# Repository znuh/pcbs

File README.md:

# pcbs
various printed circuit boards

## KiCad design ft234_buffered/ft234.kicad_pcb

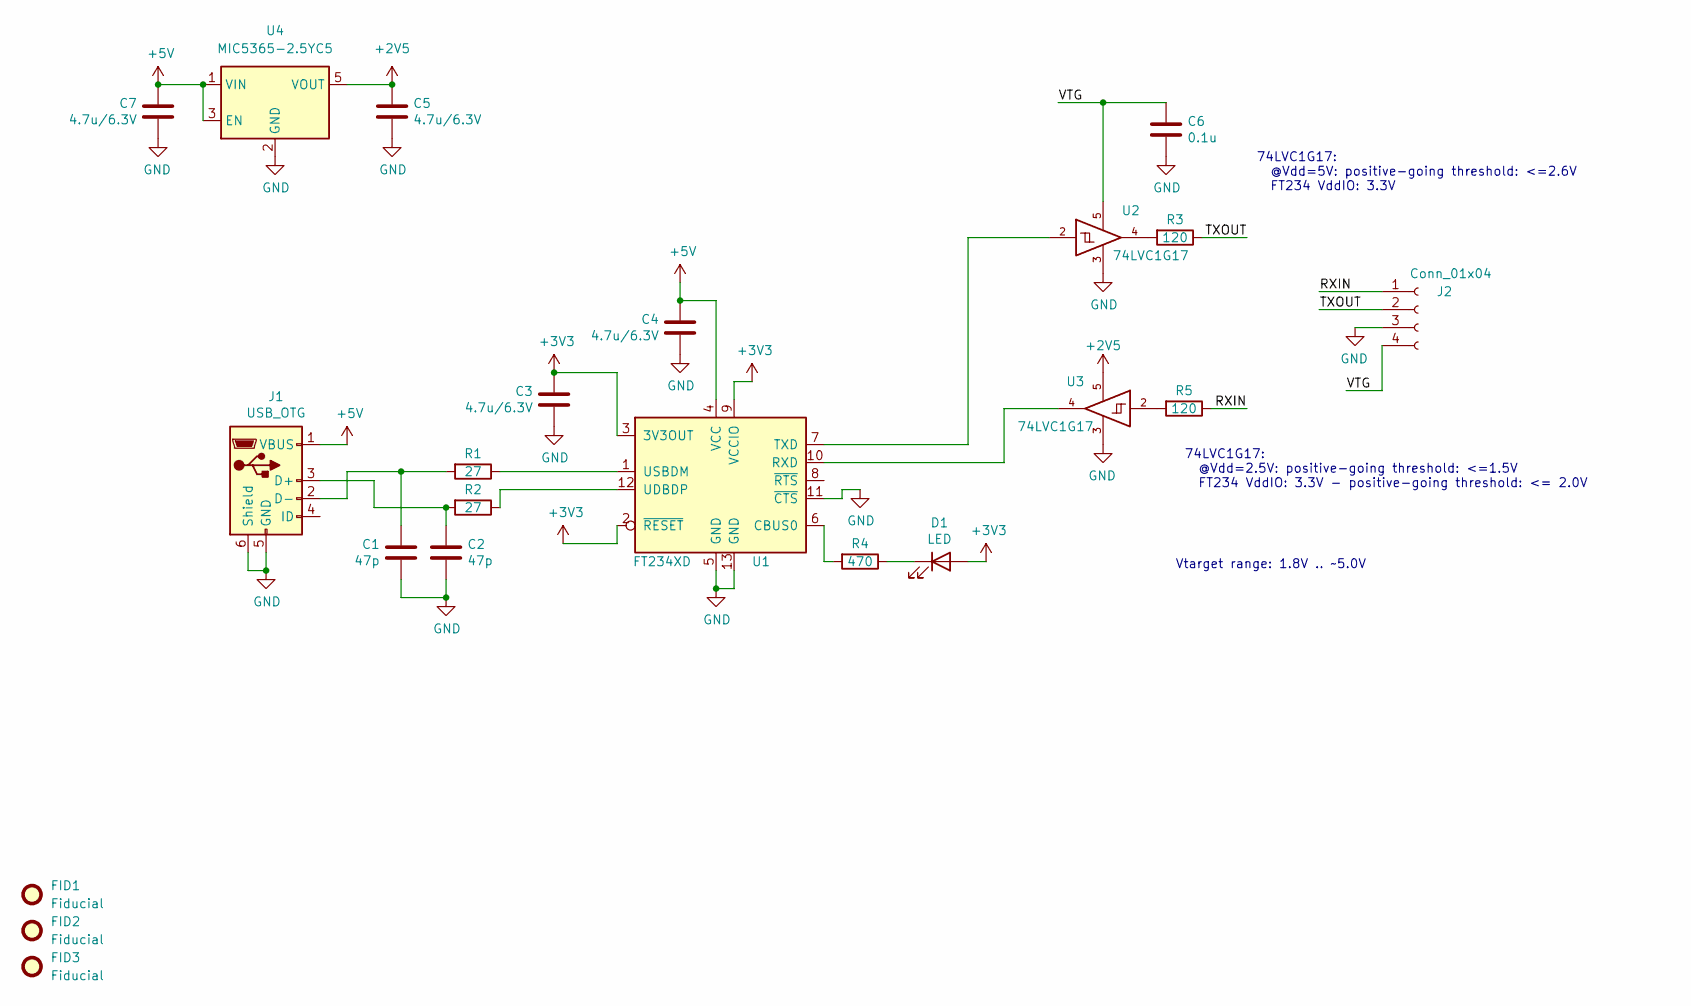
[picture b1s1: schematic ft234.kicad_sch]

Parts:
C1, C2: 47p; C_0402_1005Metric
C3, C4, C5, C7: 4.7u/6.3V; C_0402_1005Metric
C6: 0.1u; C_0402_1005Metric
D1: LED; LED_0603_1608Metric
FID1, FID2, FID3: Fiducial; Fiducial_0.5mm_Mask1mm
J1: USB_OTG; USB_Micro-B_Amphenol_10103594-0001LF_Horizontal
J2: Conn_01x04; PinHeader_1x04_P2.54mm_Vertical
R1, R2: 27; R_0402_1005Metric
R3, R5: 120; R_0402_1005Metric
R4: 470; R_0402_1005Metric
U1: FT234XD; DFN-12-1EP_3x3mm_P0.45mm_EP1.66x2.38mm
U2, U3: 74LVC1G17; TSOP-5_1.65x3.05mm_P0.95mm
U4: MIC5365-2.5YC5; SOT-353_SC-70-5

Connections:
+2V5: C5.1, U3.5, U4.5 (VOUT)
+3V3: C3.1, D1.2 (A), U1.2 (~RESET), U1.3 (3V3OUT), U1.9 (VCCIO)
+5V: C4.1, C7.1, J1.1 (VBUS), U1.4 (VCC), U4.1 (VIN), U4.3 (EN)
/RXIN: J2.1, R5.1
/TXOUT: J2.2, R3.1
/VTG: C6.1, J2.4, U2.5
GND: C1.2, C2.2, C3.2, C4.2, C5.2, C6.2, C7.2, J1.5 (GND), J1.6 (Shield), J2.3, U1.5 (GND), U1.11 (~CTS), U1.13 (GND), U2.3, U3.3, U4.2 (GND)
unnamed: D1.1 (K), R4.1
unnamed: C2.1, J1.3 (D+), R2.2
unnamed: C1.1, J1.2 (D-), R1.2
unnamed: R3.2, U2.4
unnamed: R5.2, U3.2
unnamed: R4.2, U1.6 (CBUS0)
unnamed: U1.10 (RXD), U3.4
unnamed: U1.7 (TXD), U2.2
unnamed: R2.1, U1.12 (UDBDP)
unnamed: R1.1, U1.1 (USBDM)

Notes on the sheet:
74LVC1G17: @Vdd=5V: positive-going threshold: <=2.6V FT234 VddIO: 3.3V
74LVC1G17: @Vdd=2.5V: positive-going threshold: <=1.5V FT234 VddIO: 3.3V - positive-going threshold: <= 2.0V
Vtarget range: 1.8V .. ~5.0V

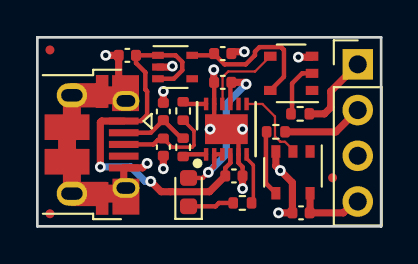
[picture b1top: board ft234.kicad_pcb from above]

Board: 2 copper layers, 19.1 x 10.5 mm, 22 parts (0 on the bottom side), 17 nets.

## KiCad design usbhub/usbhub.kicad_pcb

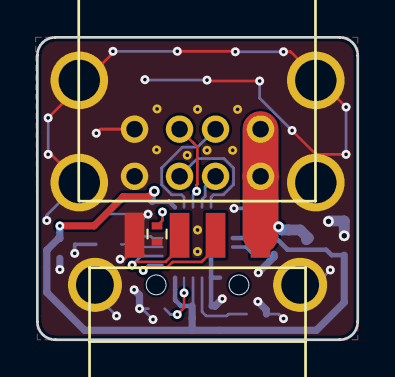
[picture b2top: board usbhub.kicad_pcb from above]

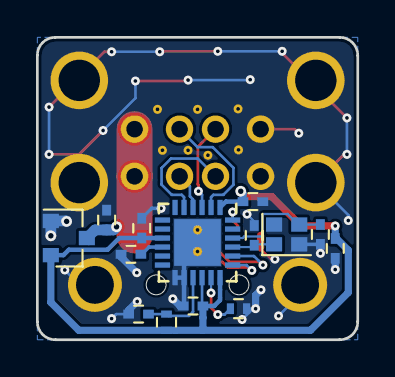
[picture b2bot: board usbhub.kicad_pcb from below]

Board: 2 copper layers, 17.8 x 16.8 mm, 17 parts (14 on the bottom side), 15 nets.

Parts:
C1, C3, C4, C5, C6, C7, C8: 1u; C_0402
C2, C9: 0.1u; C_0402
P3: USB_A; 1175-1008-ND
R1, R2: 100k; R_0402
R3: 12k; R_0402
U1: DUAL-USB
U2: AP7313SR; SOT-23
U3: USB2422; QFN-24-1EP_4x4mm_Pitch0.5mm
Y1: 24MHz; Crystal_SMD_2016-4pin_2.0x1.6mm

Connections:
+3V3: C3.1, C7.1, C8.1, C9.1, R1.1, U2.2, U3.1, U3.9, U3.16, U3.18
+5V: C1.1, P3.1, U1.1, U1.5, U2.3
/DM_DN1: U1.2, U3.2
/DM_DN2: U1.6, U3.4
/DM_UP: P3.2, U3.19
/DP_DN1: U1.3, U3.3
/DP_DN2: U1.7, U3.5
/DP_UP: P3.3, U3.20
GND: C1.2, C2.2, C3.2, C4.2, C5.2, C6.2, C7.2, C8.2, C9.2, P3.4, P3.5, R2.2, R3.2, U1.4, U1.8, U1.SH1, U1.SH2, U1.SH3, U1.SH4, U2.1, U3.13, U3.14, U3.25, Y1.2
unnamed: C2.1, R1.2, U3.15
unnamed: C4.1, U3.21, Y1.1
unnamed: C5.1, U3.22, Y1.3
unnamed: C6.1, U3.10
unnamed: R2.1, U3.17
unnamed: R3.1, U3.24

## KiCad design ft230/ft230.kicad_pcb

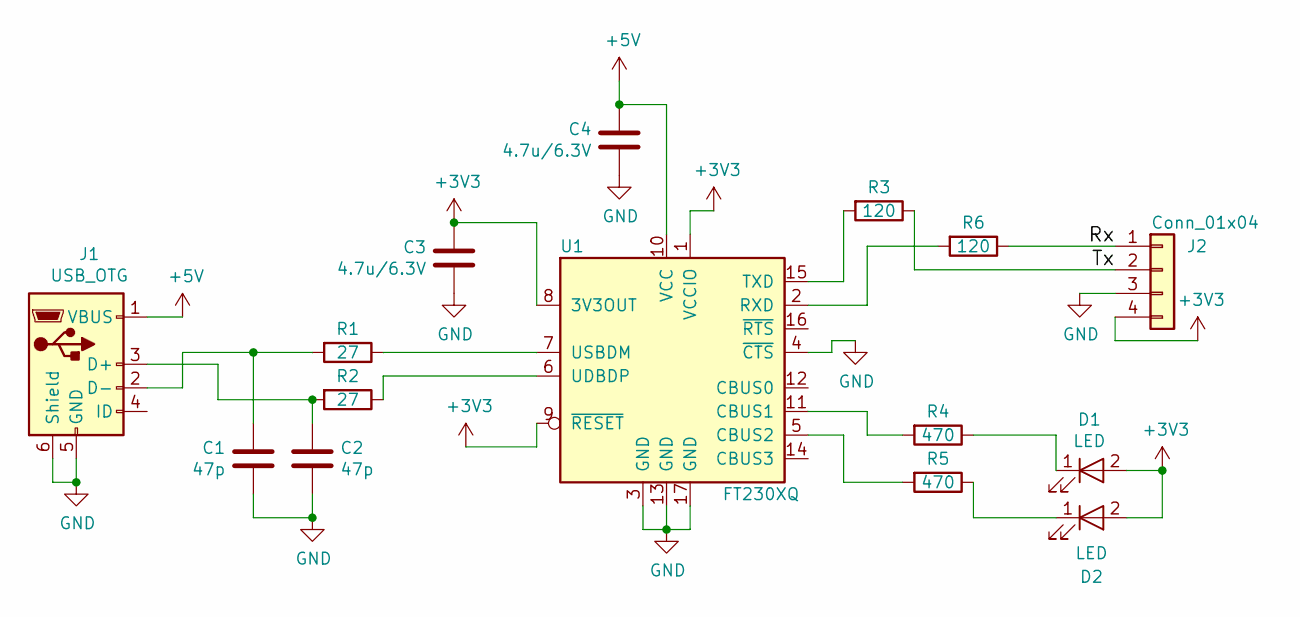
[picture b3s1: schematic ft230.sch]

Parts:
C1, C2: 47p; C_0402_NoSilk
C3, C4: 4.7u/6.3V; C_0603
D1, D2: LED; LED_0603
J1: USB_OTG; USB_Micro-B_10103594-0001LF
J2: Conn_01x04; Pin_Header_Straight_1x04_Pitch2.54mm
R1, R2: 27; R_0402_NoSilk
R3, R6: 120; R_0402_NoSilk
R4, R5: 470; R_0402_NoSilk
U1: FT230XQ; QFN-16-1EP_4x4mm_Pitch0.65mm

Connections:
+3V3: C3.1, D1.2 (A), D2.2 (A), J2.4, U1.1 (VCCIO), U1.8 (3V3OUT), U1.9 (~RESET)
+5V: C4.1, J1.1 (VBUS), U1.10 (VCC)
/Rx: J2.1, R6.1
/Tx: J2.2, R3.1
GND: C1.2, C2.2, C3.2, C4.2, J1.5 (GND), J1.6 (Shield), J2.3, U1.3 (GND), U1.4 (~CTS), U1.13 (GND), U1.17 (GND)
unnamed: C1.1, J1.2 (D-), R1.2
unnamed: C2.1, J1.3 (D+), R2.2
unnamed: D1.1 (K), R4.1
unnamed: D2.1 (K), R5.1
unnamed: R1.1, U1.7 (USBDM)
unnamed: R2.1, U1.6 (UDBDP)
unnamed: R3.2, U1.15 (TXD)
unnamed: R4.2, U1.11 (CBUS1)
unnamed: R5.2, U1.5 (CBUS2)
unnamed: R6.2, U1.2 (RXD)

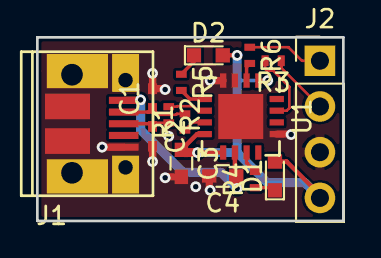
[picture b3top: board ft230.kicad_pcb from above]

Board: 2 copper layers, 17.0 x 10.2 mm, 15 parts (0 on the bottom side), 15 nets.

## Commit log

2017-09-27 add license
2017-09-27 tiny ft230 board
2017-10-24 exchange Rx and Tx
2017-10-24 add ft234 board
2019-02-18 tiny USB hub
2019-02-18 symbol and footprint tables
2019-02-18 fix 3D models
2019-03-04 xtal
2019-03-11 buffered ft234
2019-03-11 gerber settings
2023-06-04 migrate to KiCad 7
2023-06-04 changing buffered ft234 board - wip
2023-06-04 done
2023-06-04 add fiducials
2023-06-04 add better pin1 mark
2023-06-04 gerber foo
